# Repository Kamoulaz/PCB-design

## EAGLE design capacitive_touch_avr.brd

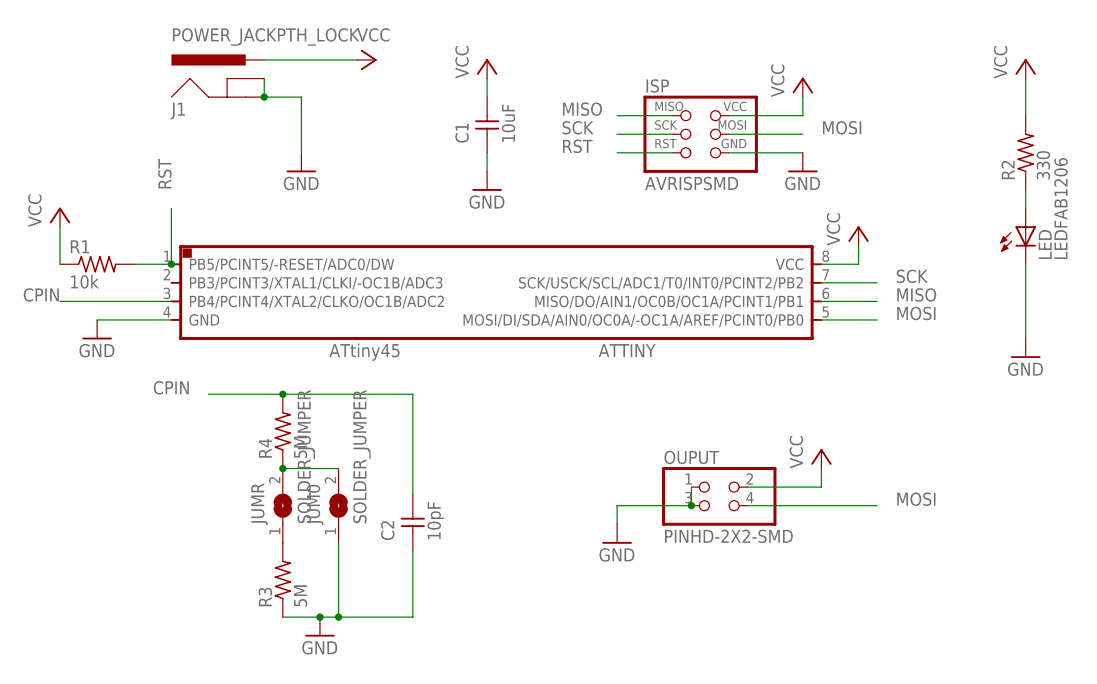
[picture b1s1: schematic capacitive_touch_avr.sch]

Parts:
ATTINY: ATTINY45SI; SOIC8
C1: 10uF; C1206FAB
C2: 10pF; C1206FAB
ISP: AVRISPSMD; 2X03SMD
J1: POWER_JACKPTH_LOCK; POWER_JACK_PTH_LOCK
JUM0: SOLDER_JUMPER; SJFAB
JUMR: SOLDER_JUMPER; SJFAB
LED: LEDFAB1206; LED1206FAB
OUPUT: PINHD-2X2-SMD; 2X02SMD
R1: 10k; R1206FAB
R2: 330; R1206FAB
R3, R4: 5M; R1206FAB

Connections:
CPIN: ATTINY.3 (PB4/PCINT4/XTAL2/CLKO/OC1B/ADC2), C2.2, R4.2
GND: ATTINY.4 (GND), C1.1, C2.1, ISP.6 (GND), J1.GND, J1.GNDBREAK, JUM0.1, LED.2 (C), OUPUT.1, OUPUT.3, R3.1
MISO: ATTINY.6 (MISO/DO/AIN1/OC0B/OC1A/PCINT1/PB1), ISP.1 (MISO)
MOSI: ATTINY.5 (MOSI/DI/SDA/AIN0/OC0A/-OC1A/AREF/PCINT0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), ISP.4 (MOSI), OUPUT.4
unnamed: JUM0.2, JUMR.2, R4.1
unnamed: JUMR.1, R3.2
unnamed: LED.1 (A), R2.1
RST: ATTINY.1 (PB5/PCINT5/-RESET/ADC0/DW), ISP.5 (RST), R1.2
SCK: ATTINY.7 (SCK/USCK/SCL/ADC1/T0/INT0/PCINT2/PB2), ISP.3 (SCK)
VCC: ATTINY.8 (VCC), C1.2, ISP.2 (VCC), J1.PWR, OUPUT.2, R1.1, R2.2

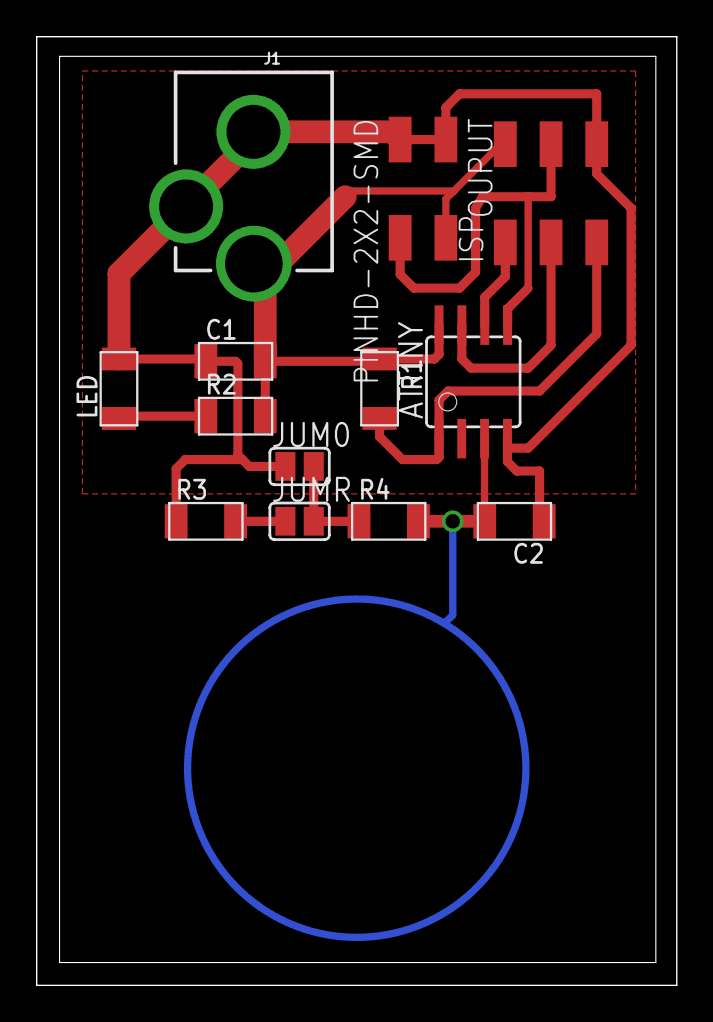
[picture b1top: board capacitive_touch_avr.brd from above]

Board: 2 copper layers, 35.6 x 52.7 mm, 13 parts (0 on the bottom side), 10 nets.

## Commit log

2018-08-10 First version. needs modifications regarding pad under the microcontroller and adding ESD shield and ground plane
2018-08-10 The same as last commit but deleting via and pad for further modifications
2018-08-11 Version 1. Touch pad + full wiring
2018-08-11 Version 2.0 isolate signals from sensor pin + pad design Missing ESD shield + Mounting holes
2018-08-17 Adding ISP and jumber at sensor R
2018-08-24 Tested and working version Modifying power jack from SMD to TH

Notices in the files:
parts and their libraries:
SparkFun-Connectors: Licensing: Creative Commons ShareAlike 4.0 International - https://creativecommons.org/licenses/by-sa/4.0
